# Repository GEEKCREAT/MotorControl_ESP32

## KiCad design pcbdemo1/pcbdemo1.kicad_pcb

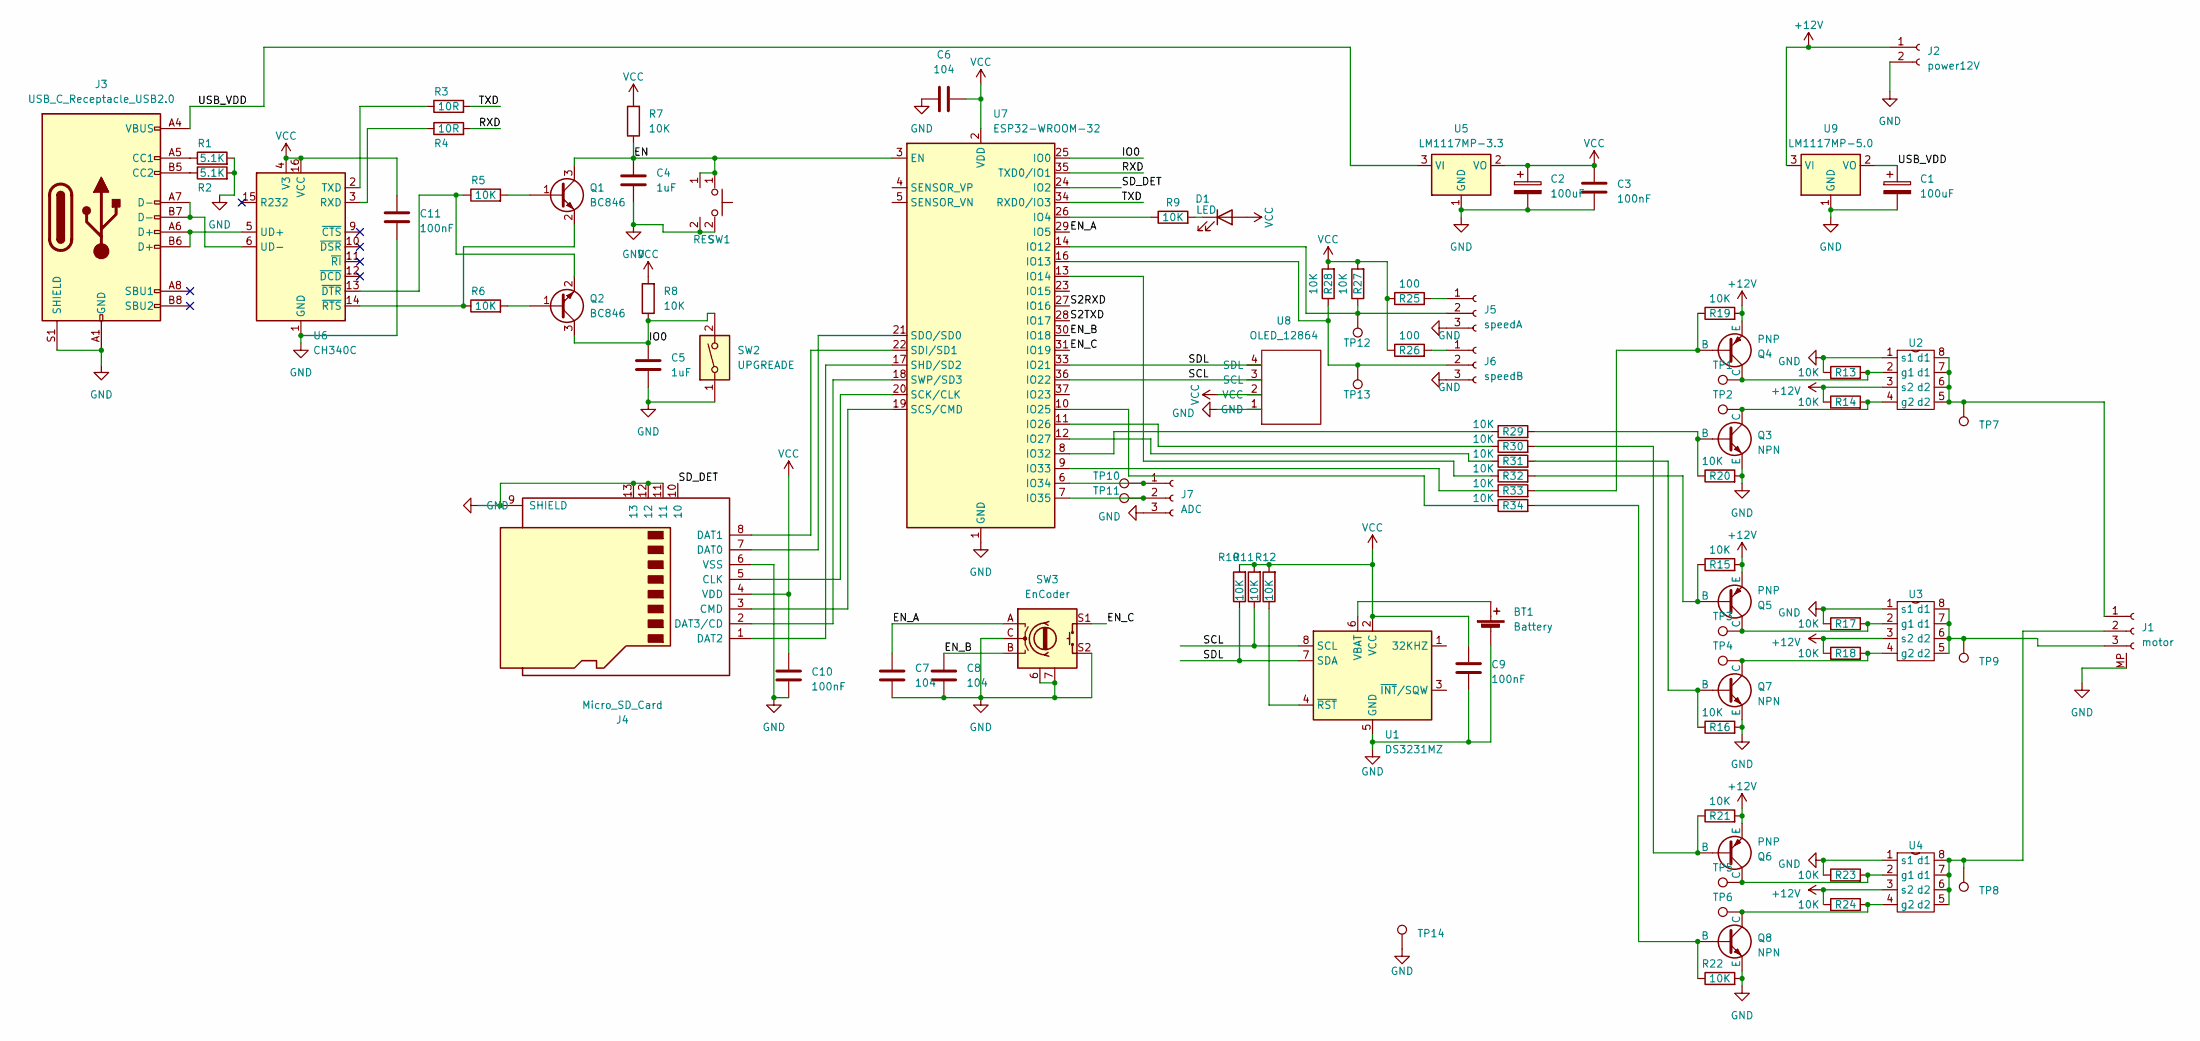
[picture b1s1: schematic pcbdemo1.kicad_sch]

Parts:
BT1: Battery; BAT_BC501SM
C1, C2: 100uF; CP_Elec_6.3x5.9
C3, C9, C10, C11: 100nF; C_0805_2012Metric
C4, C5: 1uF; C_0805_2012Metric
C6, C7, C8: 104; C_0805_2012Metric
D1: LED; LED_0603_1608Metric
J1: motor; JST_SH_BM03B-SRSS-TB_1x03-1MP_P1.00mm_Vertical
J2: power12V; JST_EH_B2B-EH-A_1x02_P2.50mm_Vertical
J3: USB_C_Receptacle_USB2.0; USB_C_Receptacle_HRO_TYPE-C-31-M-12
J4: Micro_SD_Card; 473521001_SD
J5: speedA; JST_EH_B3B-EH-A_1x03_P2.50mm_Vertical
J6: speedB; JST_EH_B3B-EH-A_1x03_P2.50mm_Vertical
J7: ADC; JST_EH_B3B-EH-A_1x03_P2.50mm_Vertical
Q1, Q2: BC846; SOT-23
Q3, Q7, Q8: NPN; SOT-23-3
Q4, Q5, Q6: PNP; SOT-23-3
R1, R2: 5.1K; R_0603_1608Metric
R3, R4: 10R; R_0603_1608Metric
R5, R6, R7, R8, R9, R10, R11, R12, R13, R14, R15, R16, R17, R18, R19, R20, R21, R22, R23, R24, R27, R28, R29, R30, R31, R32, R33, R34: 10K; R_0603_1608Metric
R25, R26: 100; R_0603_1608Metric
SW1: RES; SW_Push_1P1T_NO_CK_KSC6xxJ
SW2: UPGREADE; SW_DIP_SPSTx01_Slide_6.7x4.1mm_W6.73mm_P2.54mm_LowProfile_J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
SW3: EnCoder; EC11
TP1, TP2, TP3, TP4, TP5, TP6, TP10, TP11, TP12, TP13: TestPoint_Pad_D1.0mm
TP7, TP8, TP9: TestPoint_Loop_D1.80mm_Drill1.0mm_Beaded
TP14: TestPoint_Pad_4.0x4.0mm
U1: DS3231MZ; SOIC-8_3.9x4.9mm_P1.27mm
U2, U3, U4: SOP-8_3.76x4.96mm_P1.27mm
U5: LM1117MP-3.3; SOT-223-3_TabPin2
U6: CH340C; SOIC-16_3.9x9.9mm_P1.27mm
U7: ESP32-WROOM-32
U8: OLED_12864; OLED12864
U9: LM1117MP-5.0; SOT-223-3_TabPin2

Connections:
+12V: J2.1, Q4.2 (E), Q5.2 (E), Q6.2 (E), R14.1, R15.2, R18.1, R19.2, R21.2, R24.1, U2.3 (s2), U3.3 (s2), U4.3 (s2), U9.3 (VI)
/EN: C4.1, Q1.3 (C), R7.1, SW1.1, U7.3 (EN)
/EN_A: C7.1, SW3.A, U7.29 (IO5)
/EN_B: C8.1, SW3.B, U7.30 (IO18)
/EN_C: SW3.S1, U7.31 (IO19)
/IO0: C5.1, Q2.3 (C), R8.1, SW2.2, U7.25 (IO0)
/RXD: R4.2, U7.35 (TXD0/IO1)
/S2RXD: U7.27 (IO16)
/S2TXD: U7.28 (IO17)
/SCL: R11.1, U1.8 (SCL), U7.36 (IO22), U8.3 (SCL)
/SDL: R10.1, U1.7 (SDA), U7.33 (IO21), U8.4 (SDL)
/SD_DET: J4.10, U7.24 (IO2)
/TXD: R3.2, U7.34 (RXD0/IO3)
/USB_VDD: C1.1, J3.A4 (VBUS), J3.A9 (VBUS), J3.B4 (VBUS), J3.B9 (VBUS), U5.3 (VI), U9.2 (VO)
GND: BT1.2 (-), C1.2, C2.2, C3.2, C4.2, C5.2, C6.1, C7.2, C8.2, C9.2, C10.2, C11.2, J1.MP, J2.2, J3.A1 (GND), J3.A12 (GND), J3.B1 (GND), J3.B12 (GND), J3.S1 (SHIELD), J4.6 (VSS), J4.9 (SHIELD), J4.11, J4.12, J4.13, J5.3, J6.3, J7.3, Q3.2 (E), Q7.2 (E), Q8.2 (E), R1.2, R2.2, R13.1, R16.2, R17.1, R20.2, R22.2, R23.1, SW1.2, SW2.1, SW3.6, SW3.7, SW3.C, SW3.S2, TP14.1, U1.5 (GND), U2.1 (s1), U3.1 (s1), U4.1 (s1), U5.1 (GND), U6.1 (GND), U7.1 (GND), U7.15 (GND), U7.38 (GND), U7.39 (GND), U8.1 (GND), U9.1 (GND)
unnamed: BT1.1 (+), U1.6 (VBAT)
unnamed: D1.1 (K), R9.2
unnamed: J1.1, TP7.1, U2.5 (d2), U2.6 (d2), U2.7 (d1), U2.8 (d1)
unnamed: J1.2, TP8.1, U4.5 (d2), U4.6 (d2), U4.7 (d1), U4.8 (d1)
unnamed: J1.3, TP9.1, U3.5 (d2), U3.6 (d2), U3.7 (d1), U3.8 (d1)
unnamed: J3.A5 (CC1), R1.1
unnamed: J3.B5 (CC2), R2.1
unnamed: J4.5 (CLK), U7.20 (SCK/CLK)
unnamed: J4.3 (CMD), U7.19 (SCS/CMD)
unnamed: J4.7 (DAT0), U7.21 (SDO/SD0)
unnamed: J4.8 (DAT1), U7.22 (SDI/SD1)
unnamed: J4.1 (DAT2), U7.17 (SHD/SD2)
unnamed: J4.2 (DAT3/CD), U7.18 (SWP/SD3)
unnamed: J5.1, R25.2
unnamed: J5.2, R27.1, TP12.1, U7.14 (IO12)
unnamed: J6.1, R26.2
unnamed: J6.2, R28.1, TP13.1, U7.16 (IO13)
unnamed: J7.1, TP10.1, U7.6 (IO34)
unnamed: J7.2, TP11.1, U7.7 (IO35)
unnamed: Q1.1 (B), R5.2
unnamed: Q1.2 (E), R6.1, U6.14 (~RTS)
unnamed: Q2.1 (B), R6.2
unnamed: Q2.2 (E), R5.1, U6.13 (~DTR)
unnamed: Q3.1 (B), R20.1, R29.2
unnamed: Q3.3 (C), R14.2, TP2.1, U2.4 (g2)
unnamed: Q4.1 (B), R19.1, R33.2
unnamed: Q4.3 (C), R13.2, TP1.1, U2.2 (g1)
unnamed: Q5.1 (B), R15.1, R32.2
unnamed: Q5.3 (C), R17.2, TP3.1, U3.2 (g1)
unnamed: Q6.1 (B), R21.1, R30.2
unnamed: Q6.3 (C), R23.2, TP5.1, U4.2 (g1)
unnamed: Q7.1 (B), R16.1, R31.2
unnamed: Q7.3 (C), R18.2, TP4.1, U3.4 (g2)
unnamed: Q8.1 (B), R22.1, R34.2
unnamed: Q8.3 (C), R24.2, TP6.1, U4.4 (g2)
unnamed: R12.1, U1.4 (~RST)
unnamed: R4.1, U6.3 (RXD)
unnamed: R3.1, U6.2 (TXD)
unnamed: J3.A6 (D+), J3.B6 (D+), U6.5 (UD+)
unnamed: J3.A7 (D-), J3.B7 (D-), U6.6 (UD-)
unnamed: R9.1, U7.26 (IO4)
unnamed: R32.1, U7.13 (IO14)
unnamed: R34.1, U7.10 (IO25)
unnamed: R30.1, U7.11 (IO26)
unnamed: R31.1, U7.12 (IO27)
unnamed: R29.1, U7.8 (IO32)
unnamed: R33.1, U7.9 (IO33)
VCC: C2.1, C3.1, C6.2, C9.1, C10.1, C11.1, D1.2 (A), J4.4 (VDD), R7.2, R8.2, R10.2, R11.2, R12.2, R25.1, R26.1, R27.2, R28.2, U1.2 (VCC), U5.2 (VO), U6.4 (V3), U6.16 (VCC), U7.2 (VDD), U8.2 (VCC)

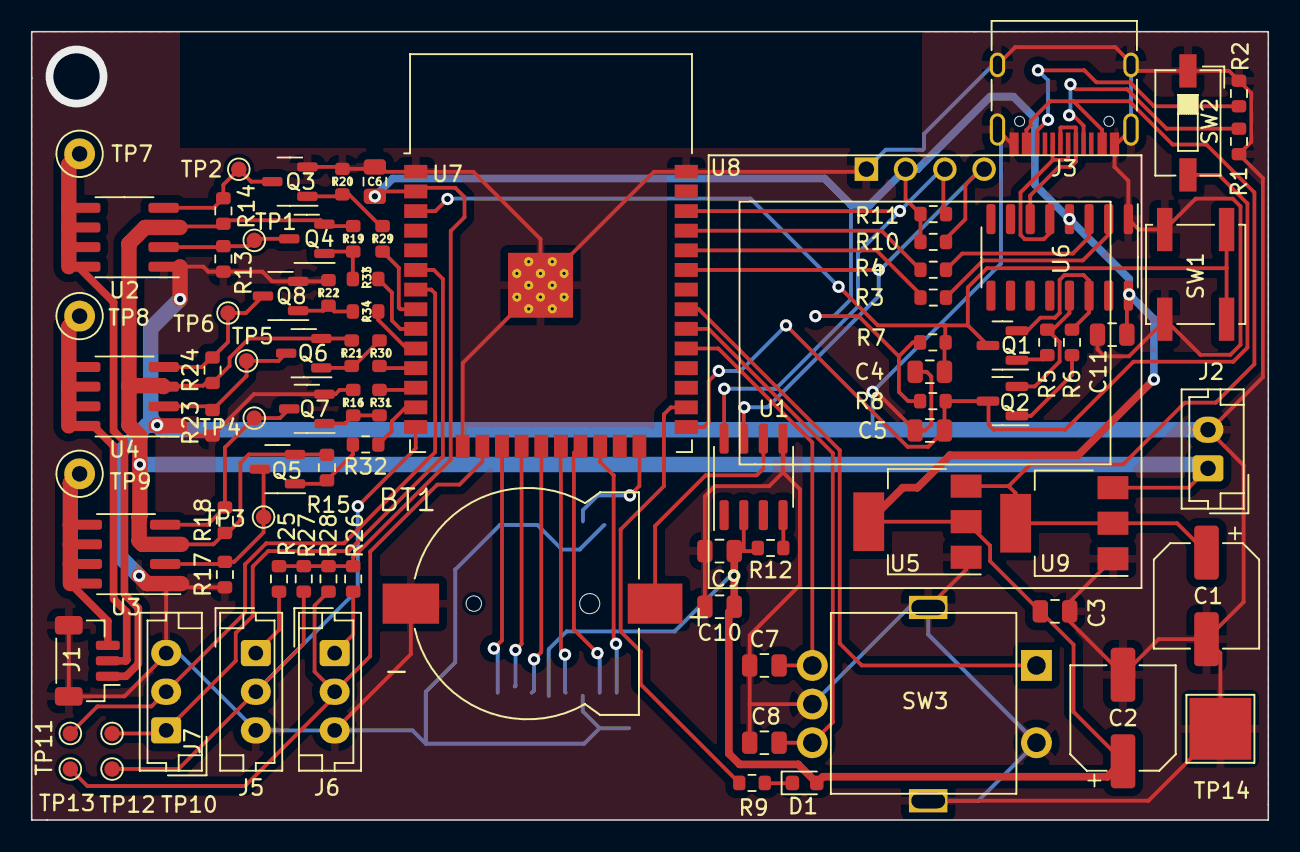
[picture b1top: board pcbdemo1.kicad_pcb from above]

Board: 2 copper layers, 80.0 x 51.0 mm, 88 parts (1 on the bottom side), 61 nets.

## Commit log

2023-05-15 new project Signed-off-by: kevin <wuwenfengmi@outlook.com>
2023-05-20 updata PCB Signed-off-by: fong <wuwenfengmi@outlook.com>
2023-05-22 测试代码

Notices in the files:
parts and their libraries:
Copyright 2021 Accelerated Designs. All rights reserved.
